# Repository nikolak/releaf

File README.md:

<div align="center">

# Releaf

**[Downloads](https://github.com/nikolak/releaf/releases)** · [Getting started](#getting-started) · [Firmware](firmware/README.md) · [PCB](#optional-controller-board) · [Changelog](CHANGELOG.md)

</div>

---

My Nanoleaf Shapes controller died, and I wasn't about to drop €40 just to turn on my perfectly good light panels. So I built Releaf: a cheap, fully local WLED controller based on the C3 SuperMini.

I kept the goals simple:
- Keep it cheap.
- Make it easy to build.
- Use common parts.
- Keep everything local.
- Avoid heavy custom firmware.

I went a step further and made an **optional PCB** that keeps the footprint small. Technically, you just need a C3 SuperMini (about 2 bucks), a resistor (cents), some wire (cents), and either a step-down converter to power the C3 SuperMini via the panel power, or just power it via USB-C if you don't mind the extra cable. The full build with the PCB and everything comes to about €7-€9 depending on where you source your hardware, shipping costs, etc.

| | |
| --- | --- |
|  |  |

## Downloads

No need to compile the firmware yourself—just grab the binaries from the [latest releases](https://github.com/nikolak/releaf/releases):

| File | What it's for |
| --- | --- |
| `releaf-esp32c3-factory.bin` | First installation over USB, including the bootloader and partition table |
| `releaf-esp32c3.bin` | Updating an existing Releaf installation through WLED |
| `releaf-gerbers.zip` | Ordering the optional PCB |
| `releaf-shell.3mf` | 3D printing the shell (Bambu Studio project with both halves). The STEP files are in [hardware/shell](hardware/shell). |

The [firmware instructions](firmware/README.md#installing-a-release) cover flashing the downloaded files. Changes between versions are in the [changelog](CHANGELOG.md).

## Getting started

You can wire this directly, use a breadboard, or make the [controller board](#optional-controller-board) below. The firmware is the same for all three.

1. Grab a release and follow the [firmware instructions](firmware/README.md#installing-a-release) to flash the C3. You can also [build from source](firmware/README.md#building-from-source).
2. Swap the cables: disconnect the original Nanoleaf controller and connect the C3 using the [wiring below](#wiring). The panels still use their original power supply.
3. Power on the C3 and connect to **WLED-AP** (password: `wled1234`). Open [4.3.2.1](http://4.3.2.1) and enter your Wi-Fi details.
4. Open WLED at its network address. Releaf finds the panels and their layout on its own, so you can use WLED's effects and presets as usual.

## Wiring

Connect the C3 to the panels like this:

| C3 connection | Panel connection |
| --- | --- |
| GPIO4 (TX) and GPIO5 (RX) | Both connect to DATA |
| 3.3 V through a 10 kΩ resistor | DATA (the pull-up resistor) |
| GND | GND |

WLED still needs a configured LED output, so GPIO10 is used as a dummy output. Leave it unconnected; the panels communicate through GPIO4 and GPIO5.

You can power the C3 through USB-C, or use a step down converter to get 5 V from the panel supply. **Crucial: Do not connect the panel's 41–42 V supply directly to the C3. Double-check the pinout as the linkers swap the 41v and DATA positions.**

## Optional controller board

The PCB integrates the C3 and power management into one board. It draws power directly from the panels, converting it to 5V for the C3 so you don't need an extra USB cable. All five components are through-hole and can be soldered by hand:

- ESP32-C3 SuperMini
- Pololu D45V5F5 converter
- ESP1010 switch
- 10 kΩ resistor
- 33 µF / 100 V capacitor

The [Gerber files](hardware/releaf-gerbers.zip) are ready for production. The board is 80 × 20 mm, two layers, and 1.6 mm thick. If you want to change the design, open [releaf.kicad_pro](hardware/releaf.kicad_pro) in KiCad 10.

When using the board, **switch it OFF before connecting USB, and unplug USB before switching it back ON.**

### Shell

A two-part printed shell holds the board and clips onto a panel with a standard linker. The files and print notes are in [hardware/shell](hardware/shell/README.md).

| Front | Back |
| --- | --- |
|  |  |

Next to the original Nanoleaf controller (top):

| From the front | At an angle | From the side |
| --- | --- | --- |
|  |  |  |

## Credits

The firmware is [WLED](https://github.com/wled/WLED), with a Shapes usermod adapted from [Cptmeme's Nanoleaf Shapes controller](https://github.com/Cptmeme/Nanoleaf-Shapes-controller/tree/65466c8d1d78132e2a151831517c090b4cc58161) for the ESP32-C3 SuperMini. WLED provides the effects, presets and web interface.

[MyrikLD's LeafBus](https://github.com/MyrikLD/LeafBus) documents the panel communication in [PROTOCOL.md](https://github.com/MyrikLD/LeafBus/blob/c40f929b5c09581beaedb593cc834cef8044b787/PROTOCOL.md).

## License

The original Releaf hardware and project files are [MIT licensed](LICENSE). The Shapes usermod keeps its upstream [GPL-3.0 license](firmware/LICENSE).

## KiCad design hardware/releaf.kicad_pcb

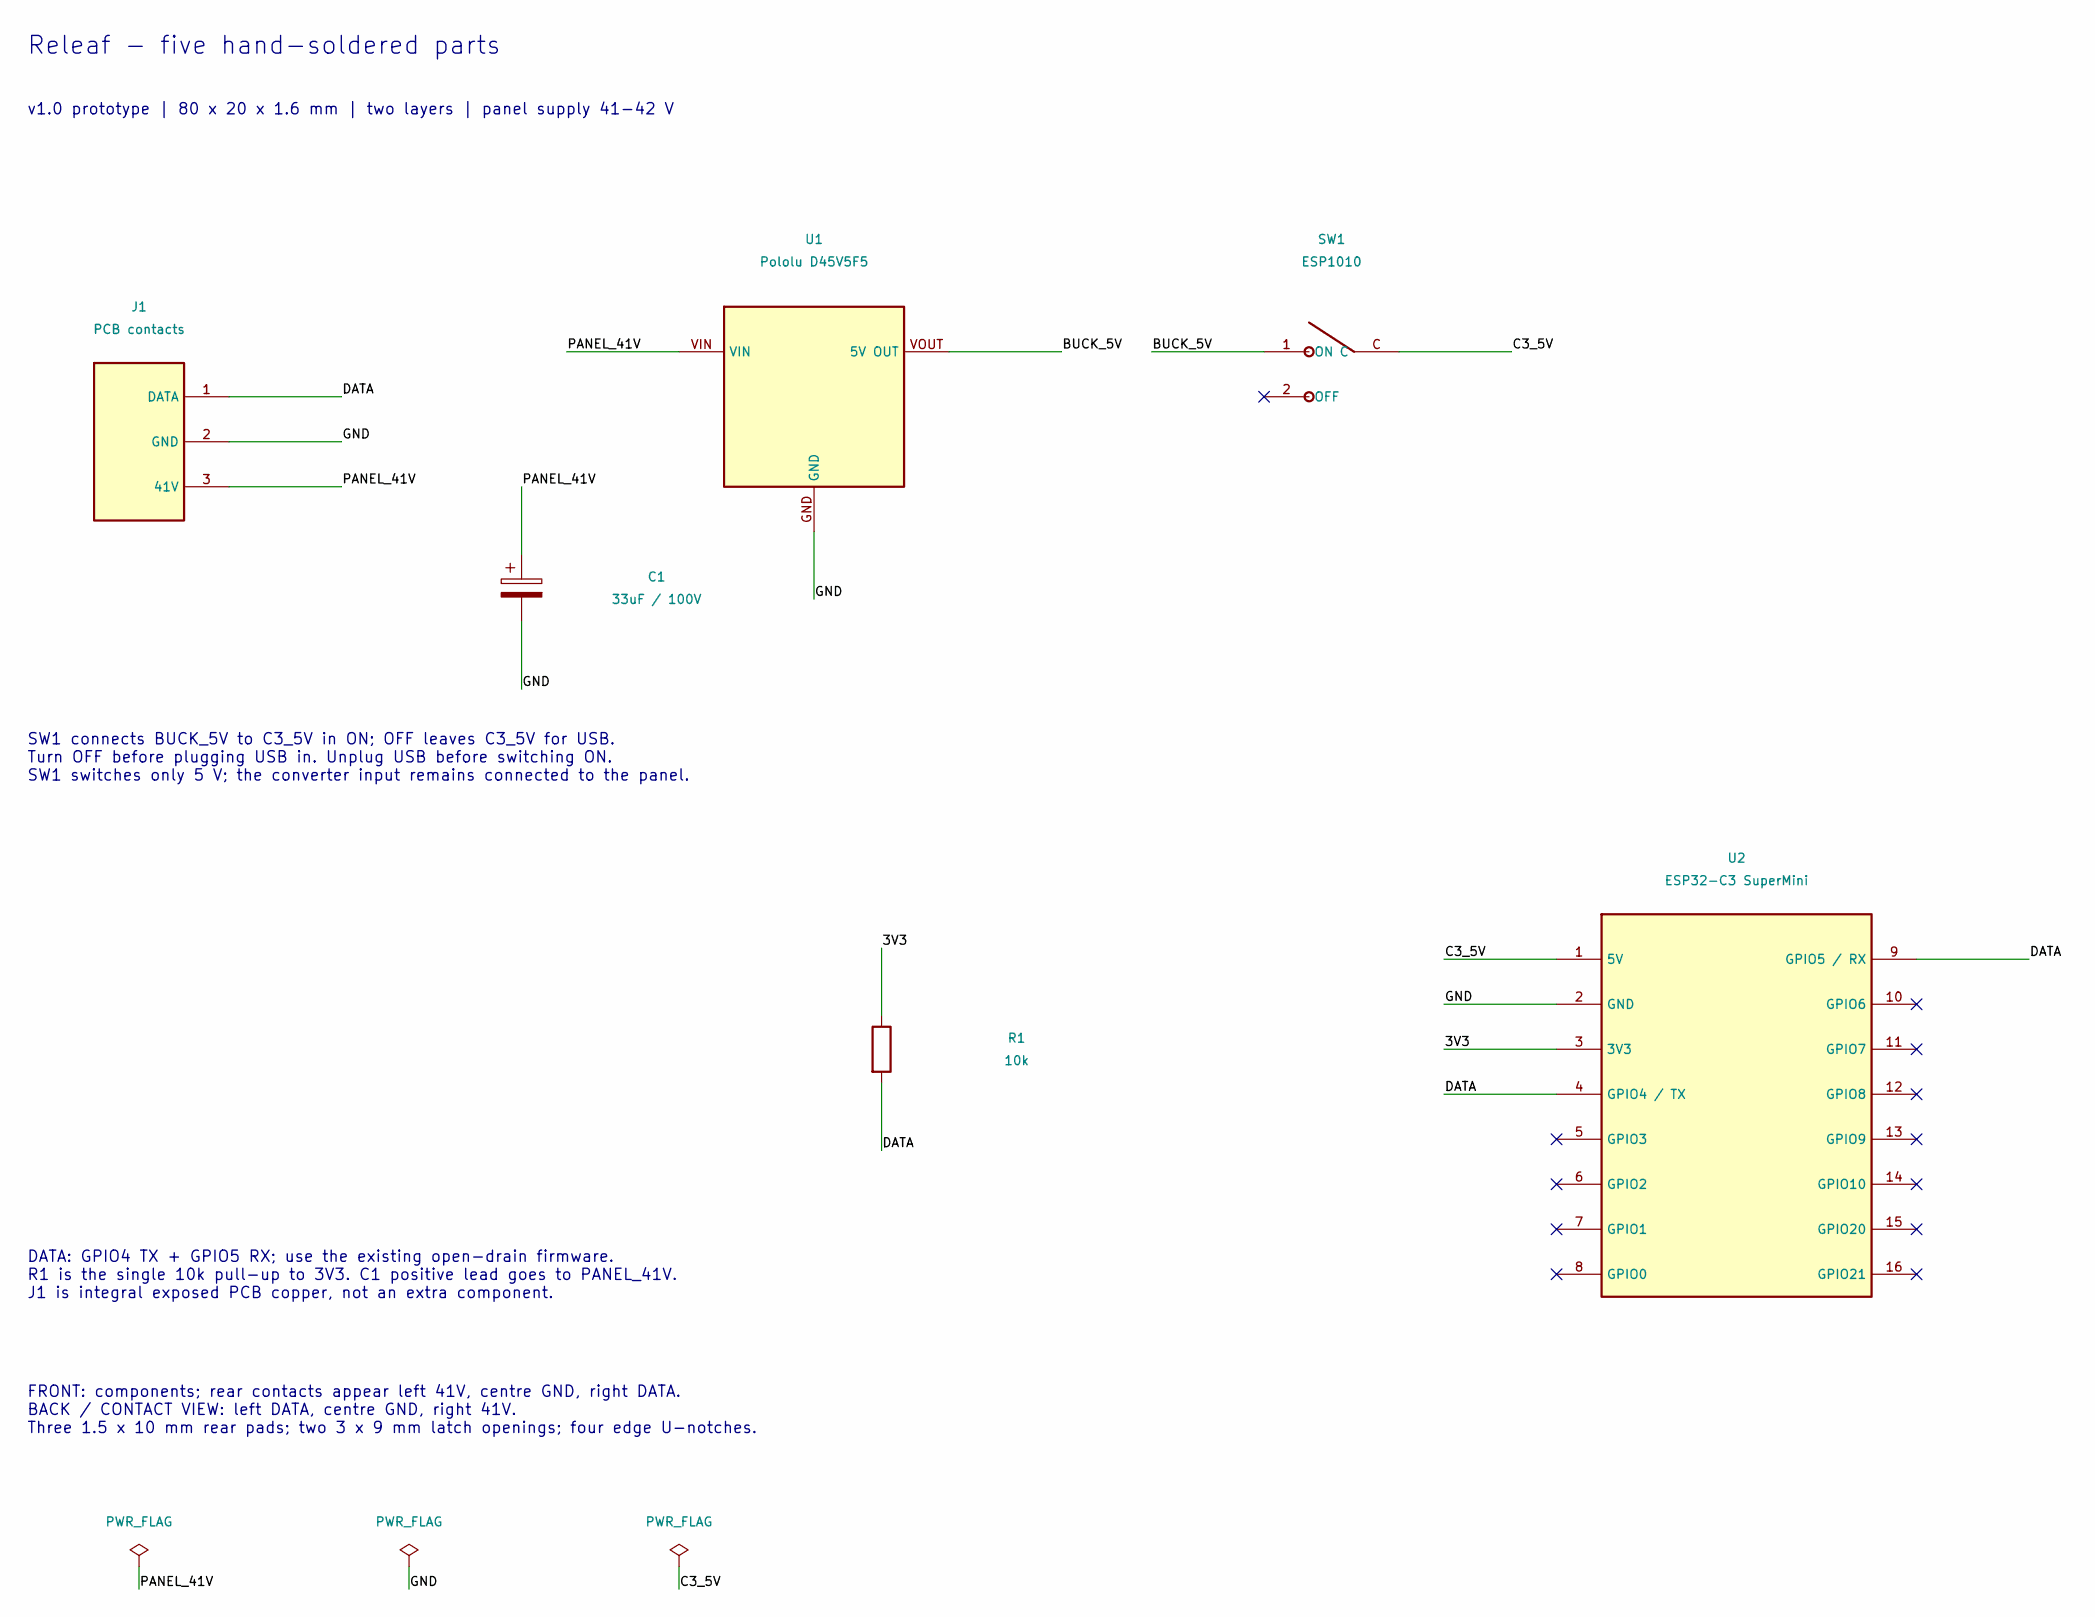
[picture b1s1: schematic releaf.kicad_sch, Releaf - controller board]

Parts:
C1: 33uF / 100V; CP_Radial_D8_L11.5_Horizontal
J1: PCB contacts; Panel_Contacts
R1: 10k; R_Axial_DIN0207_L6.3mm_D2.5mm_P7.62mm_Horizontal
SW1: ESP1010
U1: Pololu D45V5F5; D45V5F5
U2: ESP32-C3 SuperMini; ESP32_C3_SuperMini

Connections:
/3V3: R1.1, U2.3 (3V3)
/BUCK_5V: SW1.1 (ON), U1.VOUT (5V OUT)
/C3_5V: SW1.C, U2.1 (5V)
/DATA: J1.1 (DATA), R1.2, U2.4 (GPIO4 / TX), U2.9 (GPIO5 / RX)
/GND: C1.2, J1.2 (GND), U1.GND, U2.2 (GND)
/PANEL_41V: C1.1, J1.3 (41V), U1.VIN

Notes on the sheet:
Releaf - five hand-soldered parts
v1.0 prototype | 80 x 20 x 1.6 mm | two layers | panel supply 41-42 V
SW1 connects BUCK_5V to C3_5V in ON; OFF leaves C3_5V for USB. Turn OFF before plugging USB in. Unplug USB before switching ON. SW1 switches only 5 V; the converter input remains connected to the panel.
DATA: GPIO4 TX + GPIO5 RX; use the existing open-drain firmware. R1 is the single 10k pull-up to 3V3. C1 positive lead goes to PANEL_41V. J1 is integral exposed PCB copper, not an extra component.
FRONT: components; rear contacts appear left 41V, centre GND, right DATA. BACK / CONTACT VIEW: left DATA, centre GND, right 41V. Three 1.5 x 10 mm rear pads; two 3 x 9 mm latch openings; four edge U-notches.

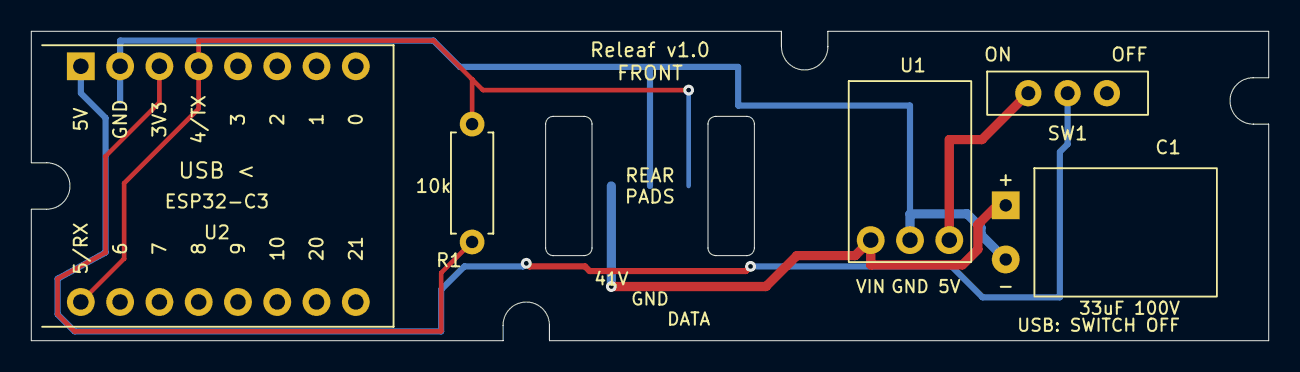
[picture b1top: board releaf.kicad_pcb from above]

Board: 2 copper layers, 80.0 x 20.0 mm, 6 parts (1 on the bottom side), 6 nets.
